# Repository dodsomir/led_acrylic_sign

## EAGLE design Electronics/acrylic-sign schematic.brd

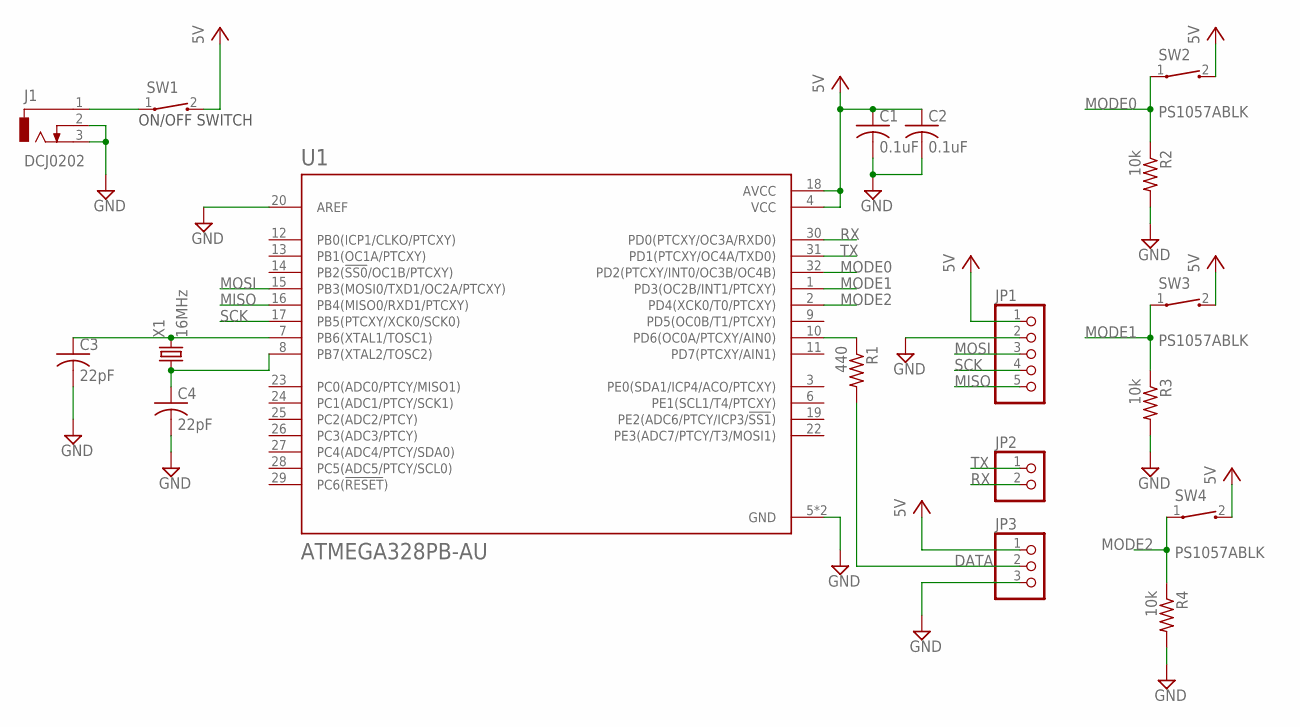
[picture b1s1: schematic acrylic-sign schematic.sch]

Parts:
C1, C2: 0.1uF; C0603
C3, C4: 22pF; C0603
J1: DCJ0202
JP1: PINHD-1X5; 1X05
JP2: PINHD-1X2; 1X02
JP3: PINHD-1X3; 1X03
R1: 440; R0603
R2, R3, R4: 10k; R0603
SW1: AMAZON_SWITCH; 1X2-3.5MM
SW2, SW3, SW4: PS1057ABLK; 1X2-3.5MM
U1: ATMEGA328PB-AU; QFP80P900X900X120-32N
X1: 16MHz; 2-SMD-5X3

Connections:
DATA: JP3.2, R1.2
GND: C1.2, C2.2, C3.2, C4.2, J1.2, J1.3, JP1.2, JP3.3, R2.2, R3.2, R4.2, U1.5 (GND), U1.20 (AREF), U1.21 (GND)
MISO: JP1.5, U1.16 (PB4(MISO0/RXD1/PTCXY))
MODE0: R2.1, SW2.1, U1.32 (PD2(PTCXY/INT0/OC3B/OC4B))
MODE1: R3.1, SW3.1, U1.1 (PD3(OC2B/INT1/PTCXY))
MODE2: R4.1, SW4.1, U1.2 (PD4(XCK0/T0/PTCXY))
MOSI: JP1.3, U1.15 (PB3(MOSI0/TXD1/OC2A/PTCXY))
unnamed: J1.1, SW1.1
unnamed: C3.1, U1.7 (PB6(XTAL1/TOSC1)), X1.2
unnamed: C4.1, U1.8 (PB7(XTAL2/TOSC2)), X1.1
unnamed: R1.1, U1.10 (PD6(OC0A/PTCXY/AIN0))
RX: JP2.2, U1.30 (PD0(PTCXY/OC3A/RXD0))
SCK: JP1.4, U1.17 (PB5(PTCXY/XCK0/SCK0))
TX: JP2.1, U1.31 (PD1(PTCXY/OC4A/TXD0))
VCC: C1.1, C2.1, JP1.1, JP3.1, SW1.2, SW2.2, SW3.2, SW4.2, U1.4 (VCC), U1.18 (AVCC)

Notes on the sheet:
ON/OFF SWITCH

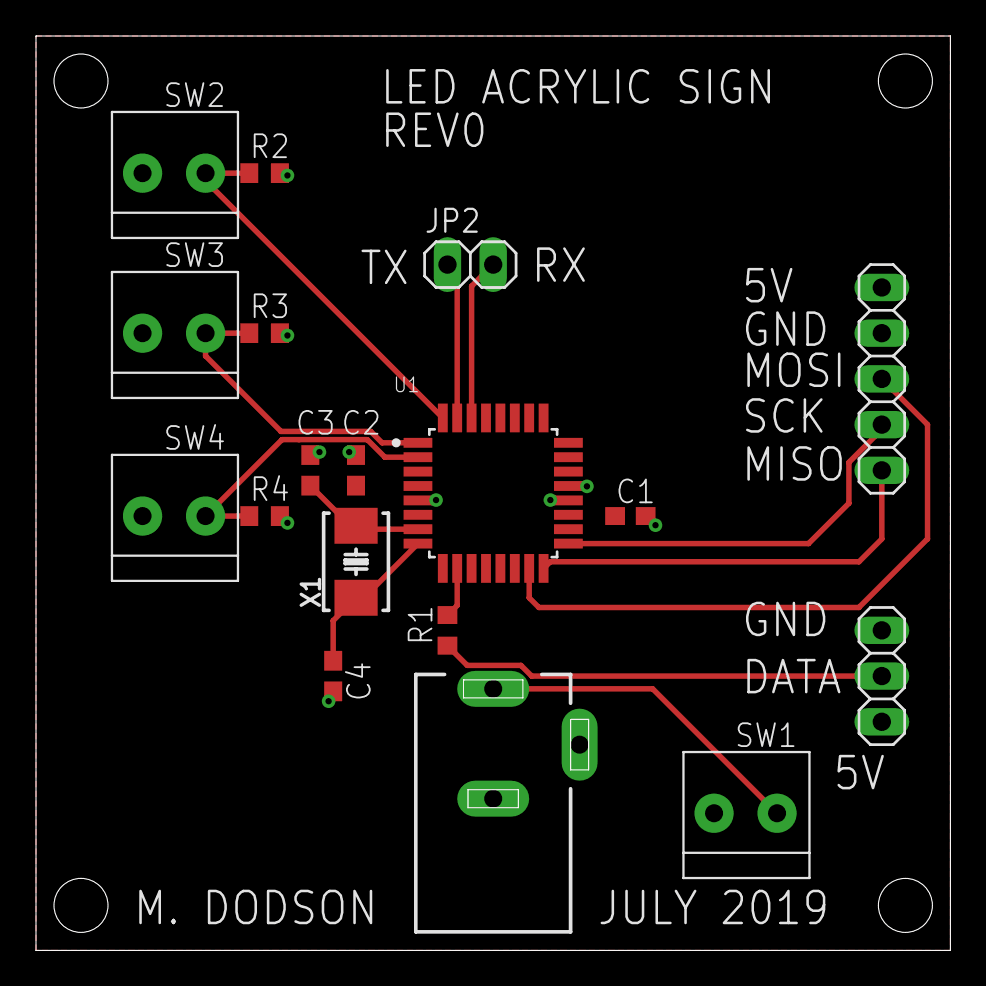
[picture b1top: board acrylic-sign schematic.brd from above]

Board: 2 copper layers, 50.8 x 50.8 mm, 18 parts (0 on the bottom side), 15 nets.

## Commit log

2019-07-27 Initial Solidworks Folder
2019-07-28 Completed Electronics REV0, Worked on more detailed Solidworks model
2019-07-28 Cleaning up folder
2019-09-26 Electronics update
